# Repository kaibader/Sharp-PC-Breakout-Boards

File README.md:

# Sharp-PC-Breakout-Boards
Various Breakout Boards for the Sharp PC-1500/1600 Series

## 40-Pin Cartridge Breakout Boards for the Sharp PC-1500/1600 Series

### v1.0
I've ported the two breakout boards from EagleCAD to KiCad.
The design of two breakout boards was also slightly improved.
There is no functional difference to the older revisions.

### v0.1
Initial release, designed in EagleCAD (which I'm not using anymore).

## Breakout Board for 60 Pin Connector of the Sharp PC-1500/PC-1600 Series
The breakout board was designed to allow easy access to all pins of the Sharp PC connector.

### v1.0
Upated the connector layout: Fixed an issue with a falsely documented FGND pin. Slight improvements in the layout.

### v0.2
Replaced the 1.27 mm pin header: the HIF6A-60PA-1.27DS is compatible with the discontinued JAE PICL-60P-LT (original Sharp-PC connector).
The whole PCB was redesigned: functional units (e.g. data bus, address bus) are now combined.

### v0.1
Initial release, based on a 1.27 mm pin header. Designed in EagleCAD (which I'm not using anymore).

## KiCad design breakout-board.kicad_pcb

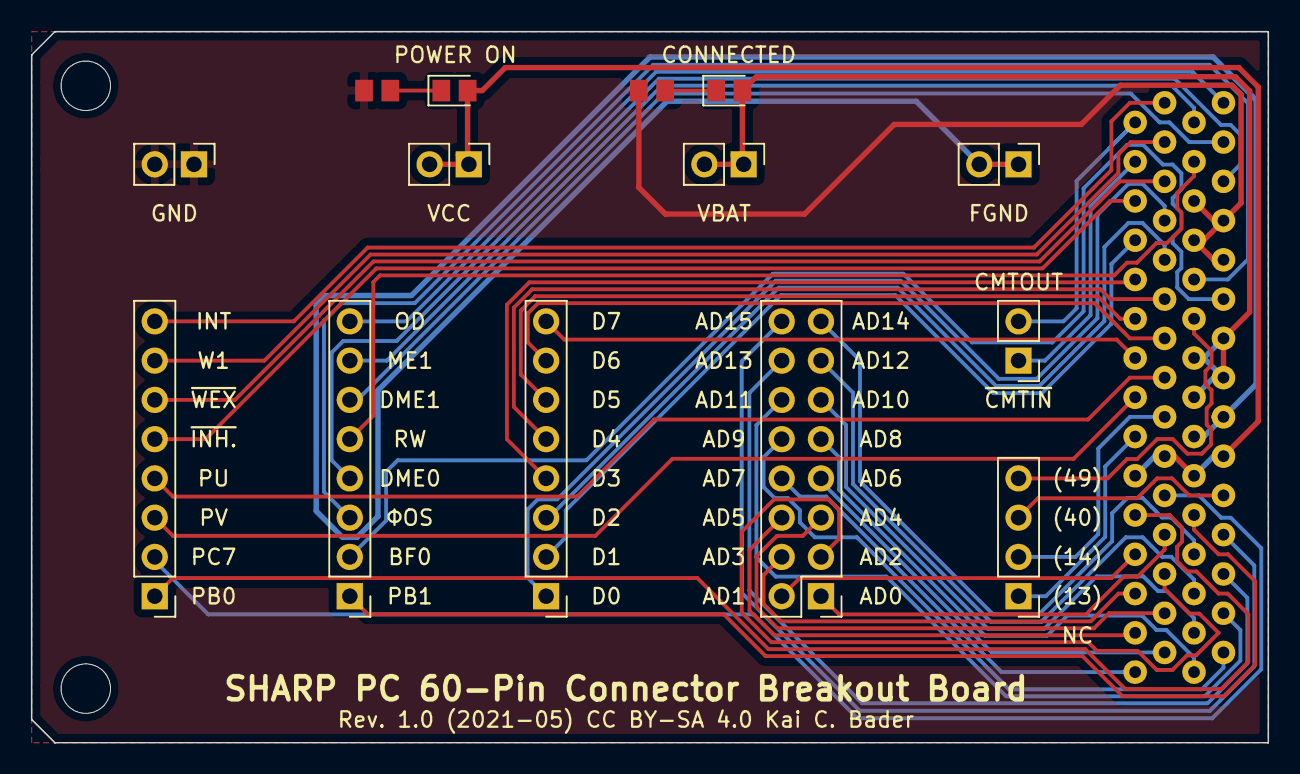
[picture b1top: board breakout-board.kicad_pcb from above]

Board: 2 copper layers, 80.0 x 46.0 mm, 17 parts (0 on the bottom side), 52 nets.

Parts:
D1: 4V7; LED_0805_2012Metric
D2: BATT; LED_0805_2012Metric
H1, H2: M3; MountingHole_3.2mm_M3
J1: NC; PinHeader_1x04_P2.54mm_Vertical
J2: PINS1; PinHeader_1x08_P2.54mm_Vertical
J3: PINS2; PinHeader_1x08_P2.54mm_Vertical
J4: CMT; PinHeader_1x02_P2.54mm_Vertical
J5: A-BUS; PinHeader_2x08_P2.54mm_Vertical
J6: D-BUS; PinHeader_1x08_P2.54mm_Vertical
J7: FGND; PinHeader_1x02_P2.54mm_Vertical
J8: 4V7; PinHeader_1x02_P2.54mm_Vertical
J9: BATT; PinHeader_1x02_P2.54mm_Vertical
J10: GND; PinHeader_1x02_P2.54mm_Vertical
P1: 60-Pin Connector; HIF6A-60PA-1.27DS
R1: 470; R_0805_2012Metric
R2: 1.2k; R_0805_2012Metric

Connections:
+4V7: D1.2, J8.1, J8.2, P1.11, P1.12, P1.41, P1.42
+BATT: D2.2, J9.1, J9.2, P1.45, P1.46, P1.47, P1.48
/AD0: J5.1, P1.8
/AD1: J5.2, P1.7
/AD2: J5.3, P1.6
/AD3: J5.4, P1.5
/AD4: J5.5, P1.4
/AD5: J5.6, P1.3
/AD6: J5.7, P1.2
/AD7: J5.8, P1.1
/AD8: J5.9, P1.31
/AD9: J5.10, P1.32
/AD10: J5.11, P1.33
/AD11: J5.12, P1.34
/AD12: J5.13, P1.35
/AD13: J5.14, P1.36
/AD14: J5.15, P1.37
/AD15: J5.16, P1.38
/BFO: J3.2, P1.50
/CMTOUT: J4.2, P1.29
/D0: J6.1, P1.24
/D1: J6.2, P1.23
/D2: J6.3, P1.22
/D3: J6.4, P1.21
/D4: J6.5, P1.20
/D5: J6.6, P1.19
/D6: J6.7, P1.18
/D7: J6.8, P1.17
/DME0: J3.4, P1.56
/DME1: J3.6, P1.58
/FGND: J7.1, J7.2, P1.43, P1.44
/INT: J2.8, P1.30
/ME1: J3.7, P1.59
/NC1: J1.1, P1.13
/NC2: J1.2, P1.14
/NC3: J1.3, P1.40
/NC4: J1.4, P1.49
/OD: J3.8, P1.60
/PB0: J2.1, P1.9
/PB1: J3.1, P1.39
/PC7: J2.2, P1.10
/PU: J2.4, P1.16
/PV: J2.3, P1.15
/RW: J3.5, P1.57
/W1: J2.7, P1.28
/~CMTIN: J4.1, P1.27
/~INHIBIT: J2.5, P1.25
/~WEX: J2.6, P1.26
/ΦOS: J3.3, P1.51
GND: J10.1, J10.2, P1.52, P1.53, P1.54, P1.55, R1.2, R2.2
unnamed: D1.1, R1.1
unnamed: D2.1, R2.1

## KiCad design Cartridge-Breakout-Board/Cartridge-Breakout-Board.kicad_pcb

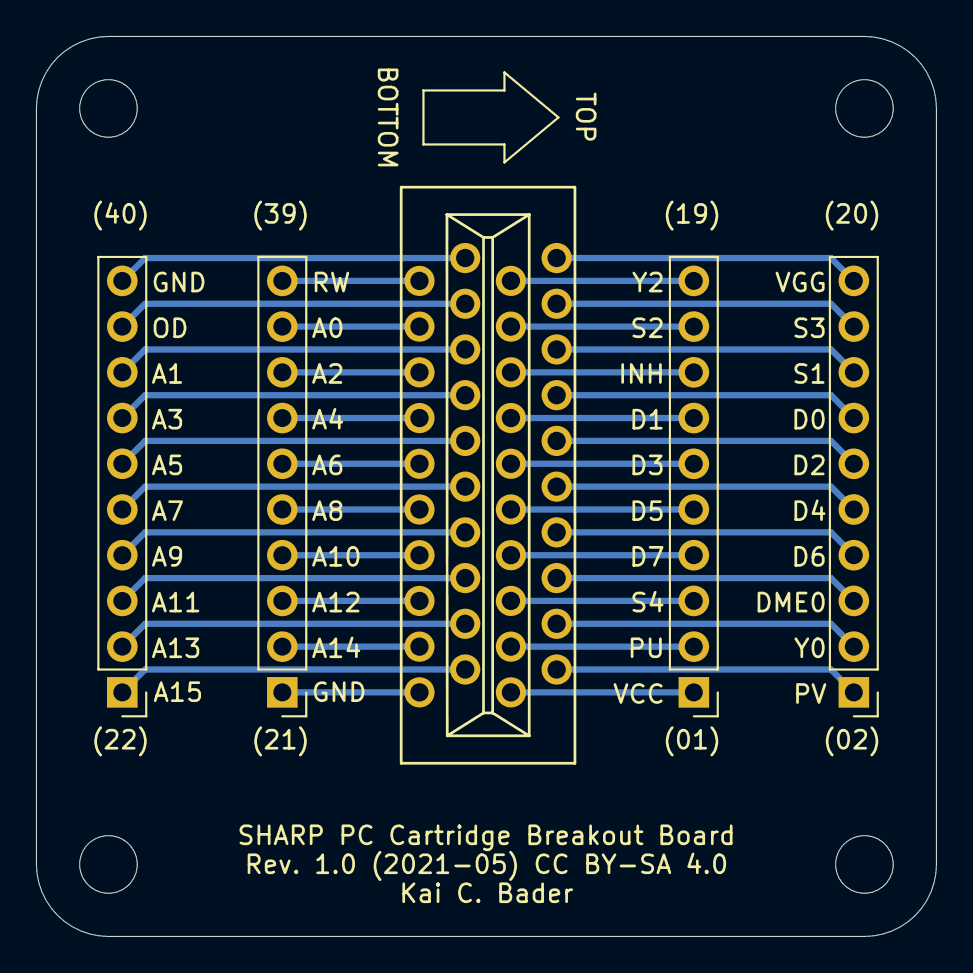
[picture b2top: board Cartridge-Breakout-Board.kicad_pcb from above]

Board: 2 copper layers, 50.0 x 50.0 mm, 9 parts (0 on the bottom side), 40 nets.

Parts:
H1, H2, H3, H4: M3; MountingHole_3.2mm_M3
J1: PINS1; PinHeader_1x10_P2.54mm_Vertical
J2: PINS2; PinHeader_1x10_P2.54mm_Vertical
J3: 40-Pin Connector; KLS1-503-40-S
J4: PINS4; PinHeader_1x10_P2.54mm_Vertical
J5: PINS3; PinHeader_1x10_P2.54mm_Vertical

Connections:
unnamed: J1.1, J3.1
unnamed: J1.2, J3.3
unnamed: J1.3, J3.5
unnamed: J1.4, J3.7
unnamed: J1.5, J3.9
unnamed: J1.6, J3.11
unnamed: J1.7, J3.13
unnamed: J1.8, J3.15
unnamed: J1.9, J3.17
unnamed: J1.10, J3.19
unnamed: J2.1, J3.21
unnamed: J2.2, J3.23
unnamed: J2.3, J3.25
unnamed: J2.4, J3.27
unnamed: J2.5, J3.29
unnamed: J2.6, J3.31
unnamed: J2.7, J3.33
unnamed: J2.8, J3.35
unnamed: J2.9, J3.37
unnamed: J2.10, J3.39
unnamed: J3.2, J4.1
unnamed: J3.4, J4.2
unnamed: J3.6, J4.3
unnamed: J3.8, J4.4
unnamed: J3.10, J4.5
unnamed: J3.12, J4.6
unnamed: J3.14, J4.7
unnamed: J3.16, J4.8
unnamed: J3.18, J4.9
unnamed: J3.20, J4.10
unnamed: J3.22, J5.1
unnamed: J3.24, J5.2
unnamed: J3.26, J5.3
unnamed: J3.28, J5.4
unnamed: J3.30, J5.5
unnamed: J3.32, J5.6
unnamed: J3.34, J5.7
unnamed: J3.36, J5.8
unnamed: J3.38, J5.9
unnamed: J3.40, J5.10

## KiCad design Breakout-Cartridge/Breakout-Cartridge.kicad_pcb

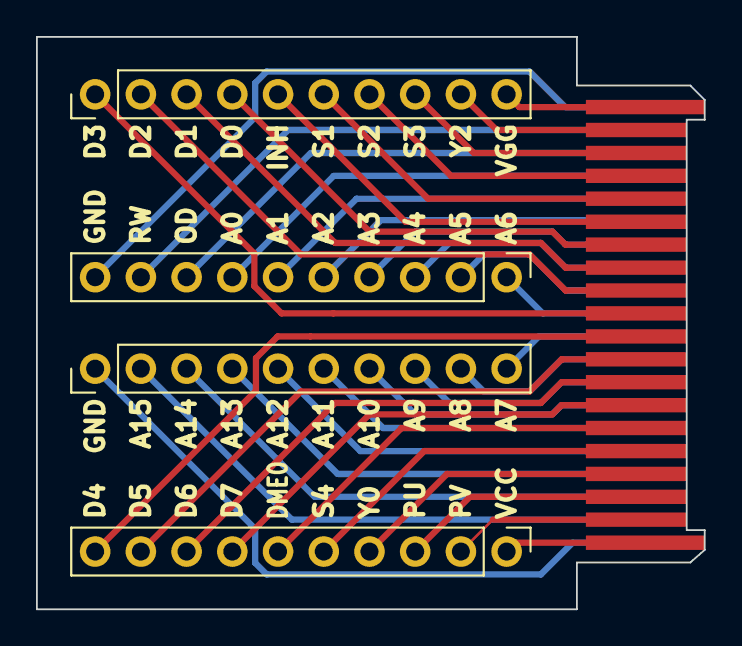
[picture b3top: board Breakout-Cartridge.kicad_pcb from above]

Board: 2 copper layers, 37.1 x 31.8 mm, 5 parts (0 on the bottom side), 40 nets.

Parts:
J1: PINS1; PinHeader_1x10_P2.54mm_Vertical
J2: PINS2; PinHeader_1x10_P2.54mm_Vertical
J3: 40-Pin Connector; SHARP-PC-CARTRIDGE
J4: PINS4; PinHeader_1x10_P2.54mm_Vertical
J5: PINS3; PinHeader_1x10_P2.54mm_Vertical

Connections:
unnamed: J1.1, J3.1
unnamed: J1.2, J3.2
unnamed: J1.3, J3.3
unnamed: J1.4, J3.4
unnamed: J1.5, J3.5
unnamed: J1.6, J3.6
unnamed: J1.7, J3.7
unnamed: J1.8, J3.8
unnamed: J1.9, J3.9
unnamed: J1.10, J3.10
unnamed: J2.1, J3.11
unnamed: J2.2, J3.12
unnamed: J2.3, J3.13
unnamed: J2.4, J3.14
unnamed: J2.5, J3.15
unnamed: J2.6, J3.16
unnamed: J2.7, J3.17
unnamed: J2.8, J3.18
unnamed: J2.9, J3.19
unnamed: J2.10, J3.20
unnamed: J3.21, J4.1
unnamed: J3.22, J4.2
unnamed: J3.23, J4.3
unnamed: J3.24, J4.4
unnamed: J3.25, J4.5
unnamed: J3.26, J4.6
unnamed: J3.27, J4.7
unnamed: J3.28, J4.8
unnamed: J3.29, J4.9
unnamed: J3.30, J4.10
unnamed: J3.31, J5.1
unnamed: J3.32, J5.2
unnamed: J3.33, J5.3
unnamed: J3.34, J5.4
unnamed: J3.35, J5.5
unnamed: J3.36, J5.6
unnamed: J3.37, J5.7
unnamed: J3.38, J5.8
unnamed: J3.39, J5.9
unnamed: J3.40, J5.10

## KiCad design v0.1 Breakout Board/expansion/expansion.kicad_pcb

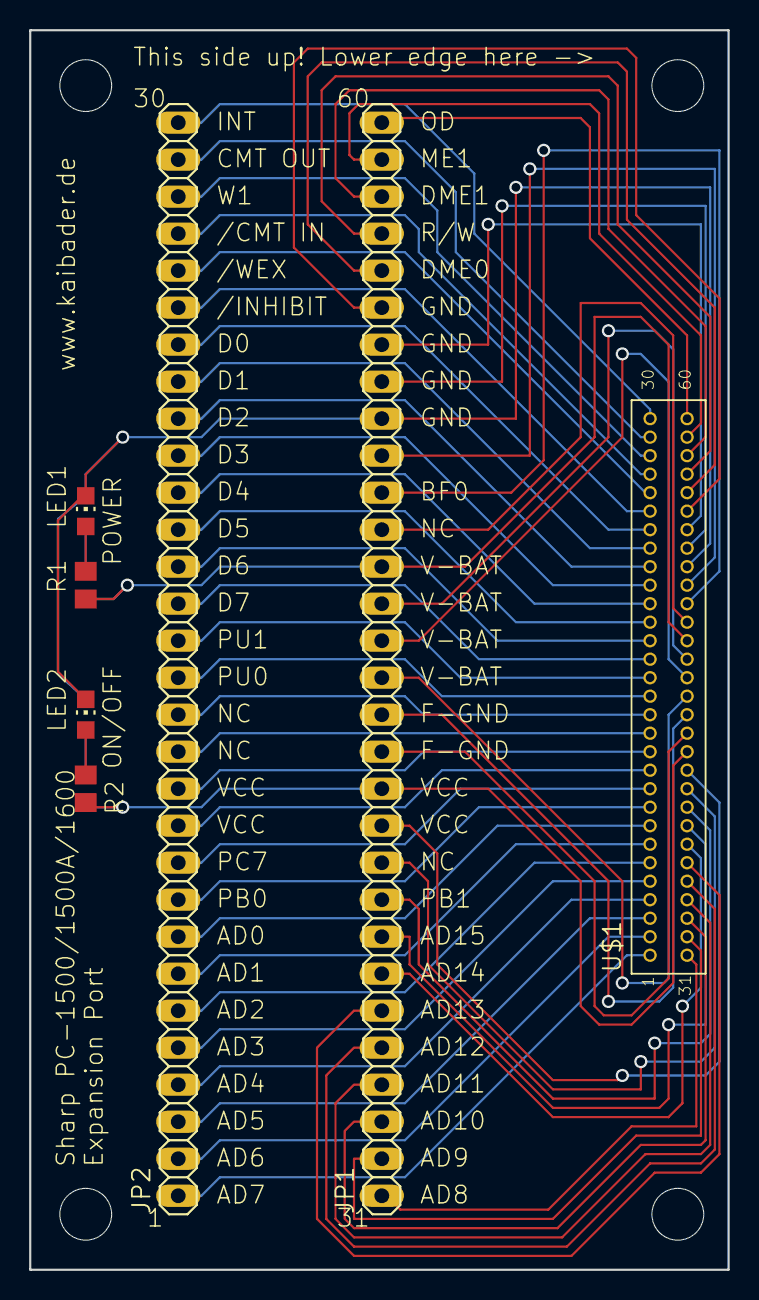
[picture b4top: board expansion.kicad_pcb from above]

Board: 2 copper layers, 47.9 x 85.1 mm, 15 parts (0 on the bottom side), 64 nets.

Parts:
@HOLE0, @HOLE1, @HOLE2, @HOLE3: (no value)
JP1, JP2: PINHD-1X30; 1X30
LED1, LED2, LED3, LED4: LEDCHIP-LED0805; CHIP-LED0805
R1, R2, R3, R4: R-EU_R0805; R0805
U$1: PINHD-2X30-2.54X1.27

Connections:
unnamed: JP1.1, U$1.1
unnamed: JP1.2, U$1.3
unnamed: JP1.3, U$1.5
unnamed: JP1.4, U$1.7
unnamed: JP1.5, U$1.9
unnamed: JP1.6, U$1.11
unnamed: JP1.7, U$1.13
unnamed: JP1.8, U$1.15
unnamed: JP1.9, U$1.17
unnamed: JP1.10, U$1.19
unnamed: JP1.11, U$1.21
unnamed: JP1.12, R2.2, R4.2, U$1.23
unnamed: JP1.13, U$1.25
unnamed: JP1.14, U$1.27
unnamed: JP1.15, U$1.29
unnamed: JP1.16, U$1.31
unnamed: JP1.17, U$1.33
unnamed: JP1.18, R1.1, R3.1, U$1.35
unnamed: JP1.19, U$1.37
unnamed: JP1.20, U$1.39
unnamed: JP1.21, U$1.41
unnamed: JP1.22, LED1.C, LED2.C, LED3.C, LED4.C, U$1.43
unnamed: JP1.23, U$1.45
unnamed: JP1.24, U$1.47
unnamed: JP1.25, U$1.49
unnamed: JP1.26, U$1.51
unnamed: JP1.27, U$1.53
unnamed: JP1.28, U$1.55
unnamed: JP1.29, U$1.57
unnamed: JP1.30, U$1.59
unnamed: JP2.1, U$1.2
unnamed: JP2.2, U$1.4
unnamed: JP2.3, U$1.6
unnamed: JP2.4, U$1.8
unnamed: JP2.5, U$1.10
unnamed: JP2.6, U$1.12
unnamed: JP2.7, U$1.14
unnamed: JP2.8, U$1.16
unnamed: JP2.9, U$1.18
unnamed: JP2.10, U$1.20
unnamed: JP2.11, U$1.22
unnamed: JP2.12, U$1.24
unnamed: JP2.13, U$1.26
unnamed: JP2.14, U$1.28
unnamed: JP2.15, U$1.30
unnamed: JP2.16, U$1.32
unnamed: JP2.17, U$1.34
unnamed: JP2.18, U$1.36
unnamed: JP2.19, U$1.38
unnamed: JP2.20, U$1.40
unnamed: JP2.21, U$1.42
unnamed: JP2.22, U$1.44
unnamed: JP2.23, U$1.46
unnamed: JP2.24, U$1.48
unnamed: JP2.25, U$1.50
unnamed: JP2.26, U$1.52
unnamed: JP2.27, U$1.54
unnamed: JP2.28, U$1.56
unnamed: JP2.29, U$1.58
unnamed: JP2.30, U$1.60
unnamed: LED1.A, R1.2
unnamed: LED2.A, R2.1
unnamed: LED3.A, R3.2
unnamed: LED4.A, R4.1

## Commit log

2016-04-16 Added The Eagle files for the Breakout Boards to a Git repository.
2017-06-07 Updated ignore list
2018-06-13 Housekeeping
    - Moved the v0.1 breakout board to a separate directory.
    - Prepared everything for a new (KiCad) based design.
2018-06-13 Created project files in KiCad
2018-06-20 Created a new version of the 60-pin Breakout Board for the Sharp PC.
2018-06-20 Added a few labels
2018-06-23 Various updates
2018-06-23 Created gerber files of the v0.2 design.
2018-06-23 Some housekeeping
2018-06-23 Updated documentation
2018-06-23 Updated the documentation
2021-05-06 Rev. 1.0 of the Sharp PC-1500 60-Pin Connector Breakout Board.
    Squashed commit of various design updates.
    Fixed one falsely documented FGND pin.
2021-05-08 Updated the two 40-Pin Breakout Boards.
    Ported the boards from EagleCAD to KiCad.
    Slightly improved the board layouts.
    No functional updates.
2021-05-13 Updated the Gerber files.

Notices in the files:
Breakout-Cartridge/Breakout-Cartridge.kicad_pcb:
CC BY-SA 4.0
Cartridge-Breakout-Board/Cartridge-Breakout-Board.kicad_pcb:
Rev. 1.0 (2021-05) CC BY-SA 4.0
breakout-board.kicad_pcb:
Rev. 1.0 (2021-05) CC BY-SA 4.0 Kai C. Bader
